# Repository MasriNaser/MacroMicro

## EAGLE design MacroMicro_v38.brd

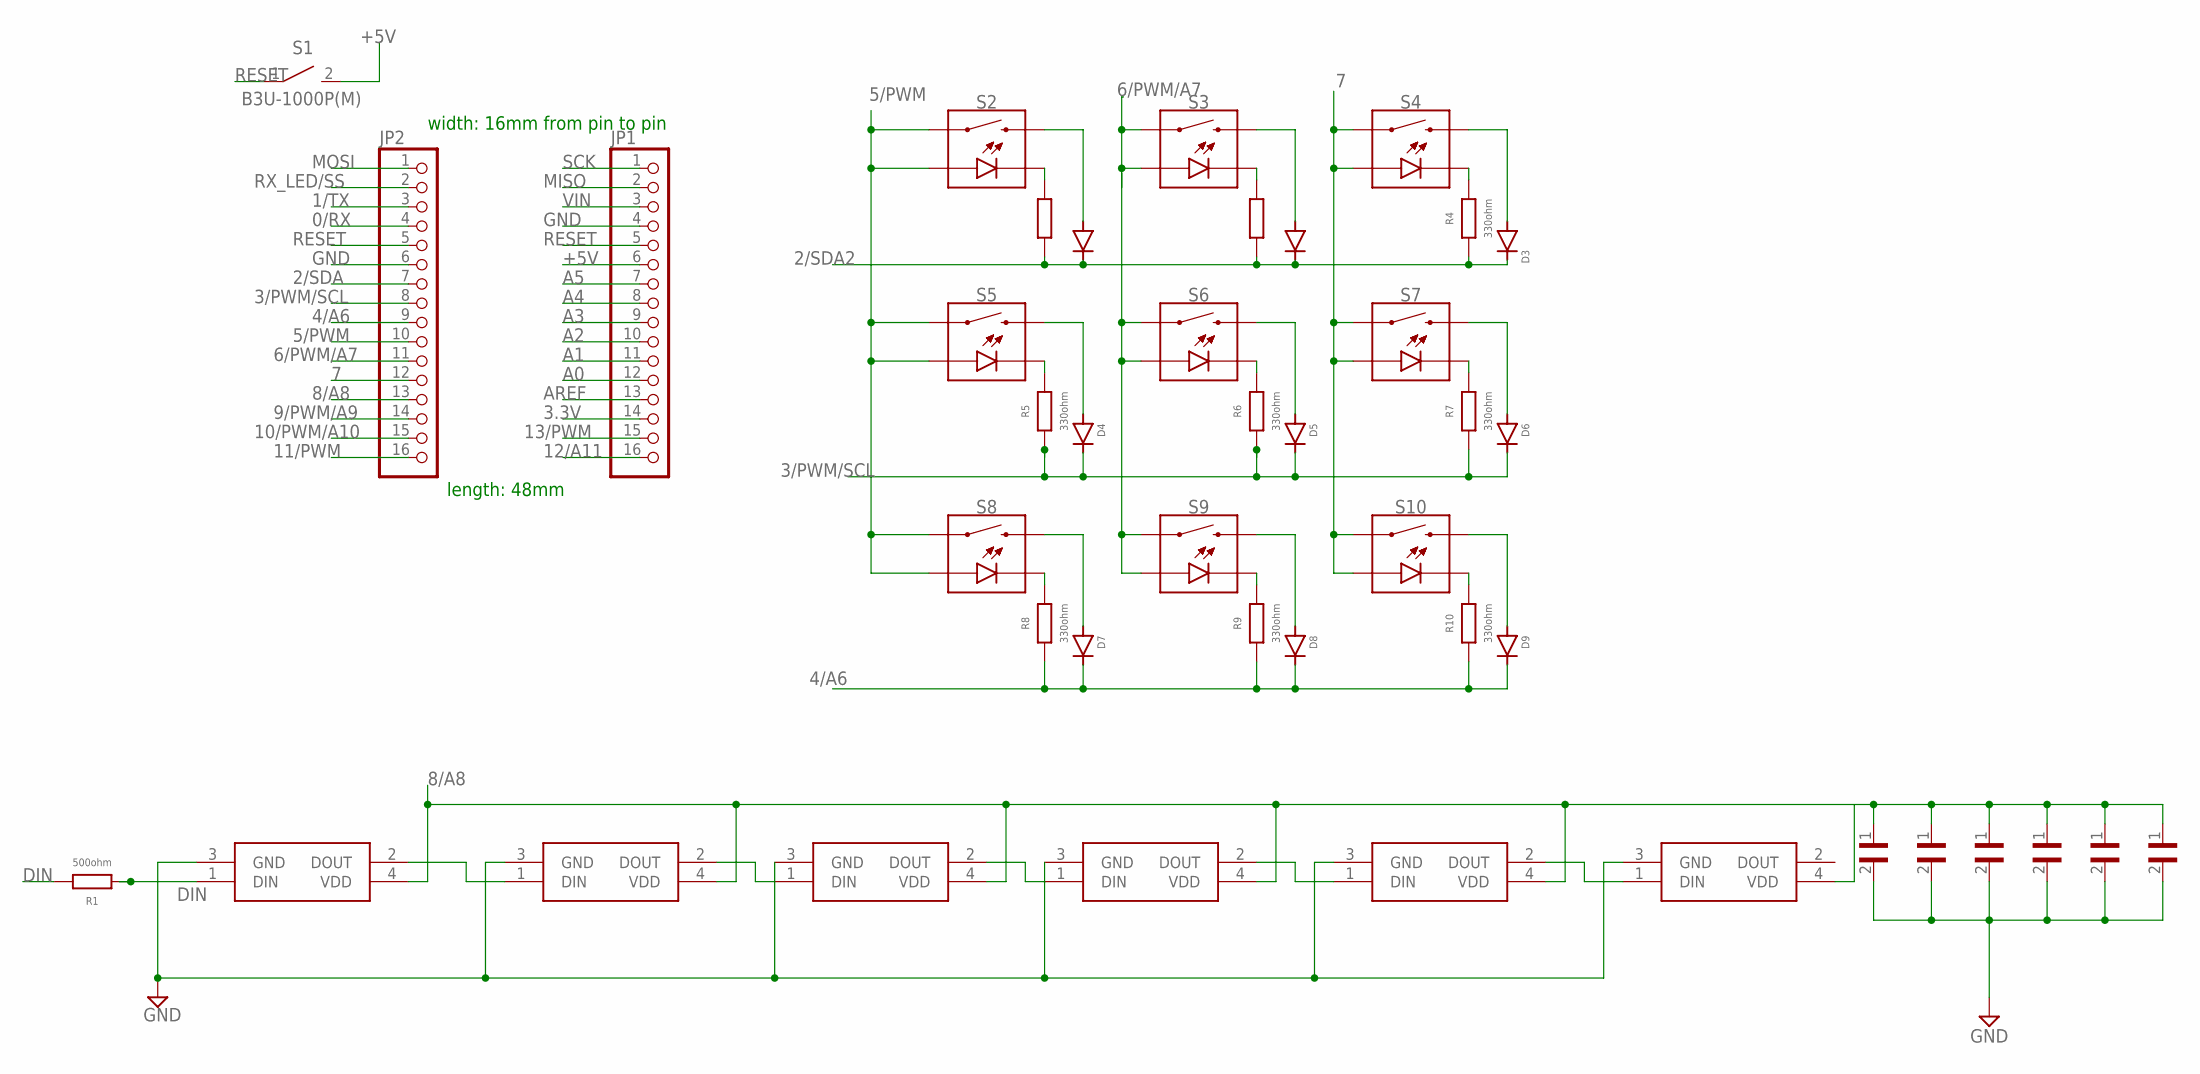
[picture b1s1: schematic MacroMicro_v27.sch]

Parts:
C1, C2, C3, C4, C5, C6: 0.1uf; CAPC1608X80N
D1, D2, D3, D4, D5, D6, D7, D8, D9: 1N4148WS; SOD-323
JP1, JP2: PINHD-1X16; 1X16
LED1, LED2, LED3, LED4, LED5, LED6: SK6812MINI-E; SK6812MINIE
R1: 500ohm; RESC3216X70
R2, R3, R4, R5, R6, R7, R8, R9, R10: 330ohm; RESC3216X70
S1: B3U-1000P(M)
S2, S3, S4, S5, S6, S7, S8, S9, S10: MOMENTARY-SWITCH-SPST-LED-PTH-CHERRY; CHERRY-MX-LED

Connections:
0/RX: JP2.4
1/TX: JP2.3
2/SDA: JP2.7
2/SDA2: D1.C, D2.C, D3.C, R2.1, R3.1, R4.1
3.3V: JP1.14
3/PWM/SCL: D4.C, D5.C, D6.C, JP2.8, R5.1, R6.1, R7.1
4/A6: D7.C, D8.C, D9.C, JP2.9, R8.1, R9.1, R10.1
5/PWM: JP2.10, S2.A, S2.S1 (1), S5.A, S5.S1 (1), S8.A, S8.S1 (1)
6/PWM/A7: JP2.11, S3.A, S3.S1 (1), S6.A, S6.S1 (1), S9.A, S9.S1 (1)
7: JP2.12, S4.A, S4.S1 (1), S7.A, S7.S1 (1), S10.A, S10.S1 (1)
8/A8: C1.1, C2.1, C3.1, C4.1, C5.1, C6.1, JP2.13, LED1.4 (VDD), LED2.4 (VDD), LED3.4 (VDD), LED4.4 (VDD), LED5.4 (VDD), LED6.4 (VDD)
9/PWM/A9: JP2.14
10/PWM/A10: JP2.15
11/PWM: JP2.16
12/A11: JP1.16
13/PWM: JP1.15
+5V: JP1.6, S1.2
A0: JP1.12
A1: JP1.11
A2: JP1.10
A3: JP1.9
A4: JP1.8
A5: JP1.7
AREF: JP1.13
DIN: LED1.1 (DIN), R1.1, R1.2
GND: C1.2, C2.2, C3.2, C4.2, C5.2, C6.2, JP1.4, JP2.6, LED1.3 (GND), LED2.3 (GND), LED3.3 (GND), LED4.3 (GND), LED5.3 (GND), LED6.3 (GND)
MISO: JP1.2
MOSI: JP2.1
unnamed: D1.A, S2.S2 (2)
unnamed: D2.A, S3.S2 (2)
unnamed: R3.2, S3.K (C)
unnamed: D3.A, S4.S2 (2)
unnamed: R4.2, S4.K (C)
unnamed: D4.A, S5.S2 (2)
unnamed: R5.2, S5.K (C)
unnamed: D5.A, S6.S2 (2)
unnamed: LED1.2 (DOUT), LED2.1 (DIN)
unnamed: R2.2, S2.K (C)
unnamed: R6.2, S6.K (C)
unnamed: LED2.2 (DOUT), LED3.1 (DIN)
unnamed: D6.A, S7.S2 (2)
unnamed: R7.2, S7.K (C)
unnamed: LED3.2 (DOUT), LED4.1 (DIN)
unnamed: D7.A, S8.S2 (2)
unnamed: R8.2, S8.K (C)
unnamed: D8.A, S9.S2 (2)
unnamed: R9.2, S9.K (C)
unnamed: D9.A, S10.S2 (2)
unnamed: R10.2, S10.K (C)
unnamed: LED4.2 (DOUT), LED5.1 (DIN)
unnamed: LED5.2 (DOUT), LED6.1 (DIN)
RESET: JP1.5, JP2.5, S1.1
RX_LED/SS: JP2.2
SCK: JP1.1
VIN: JP1.3

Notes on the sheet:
width: 16mm from pin to pin
length: 48mm

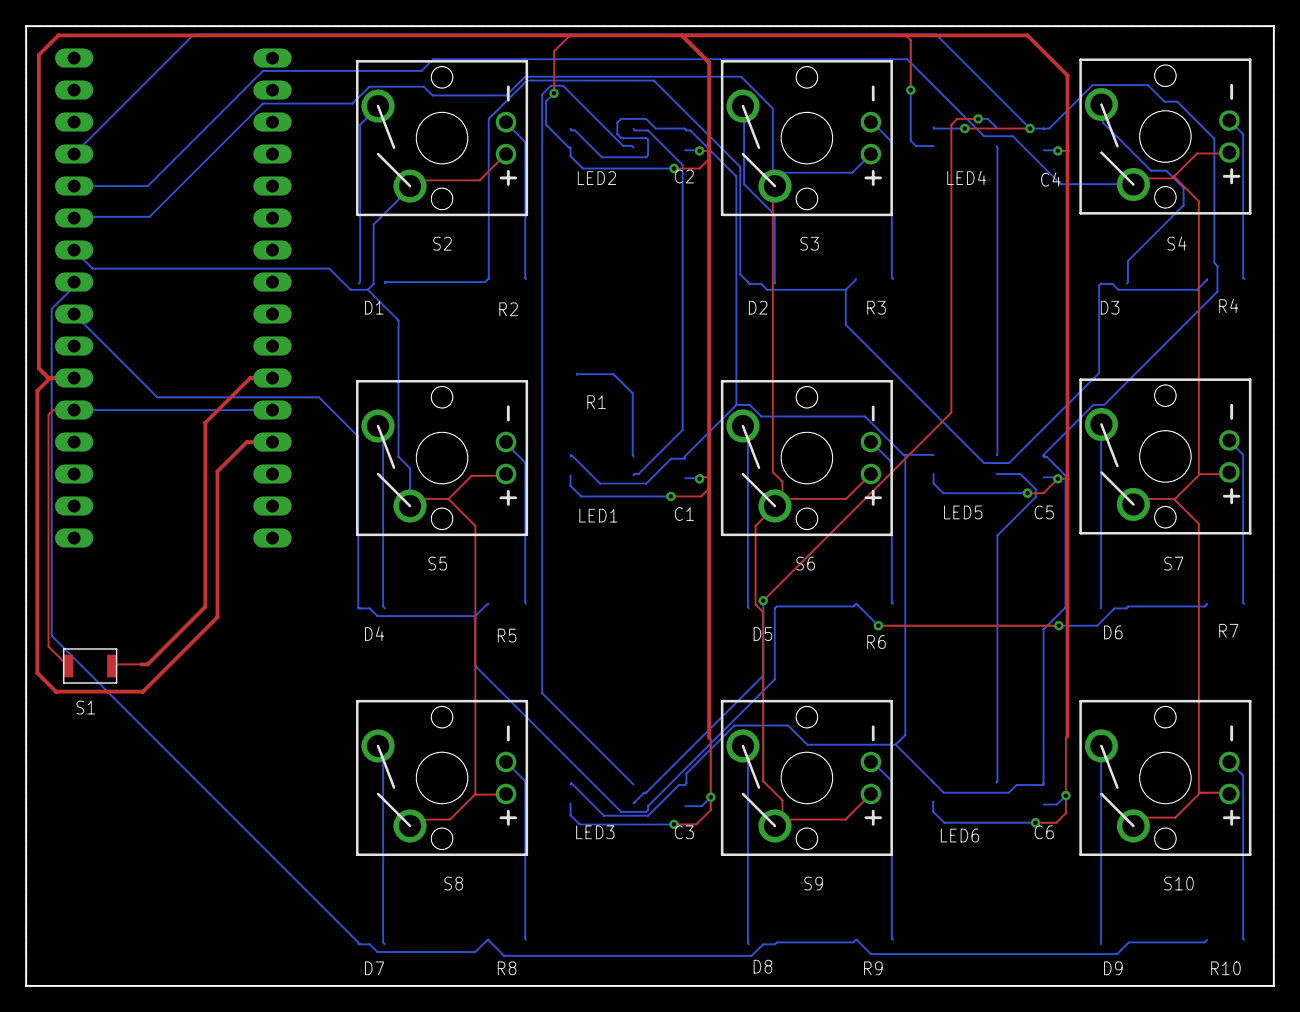
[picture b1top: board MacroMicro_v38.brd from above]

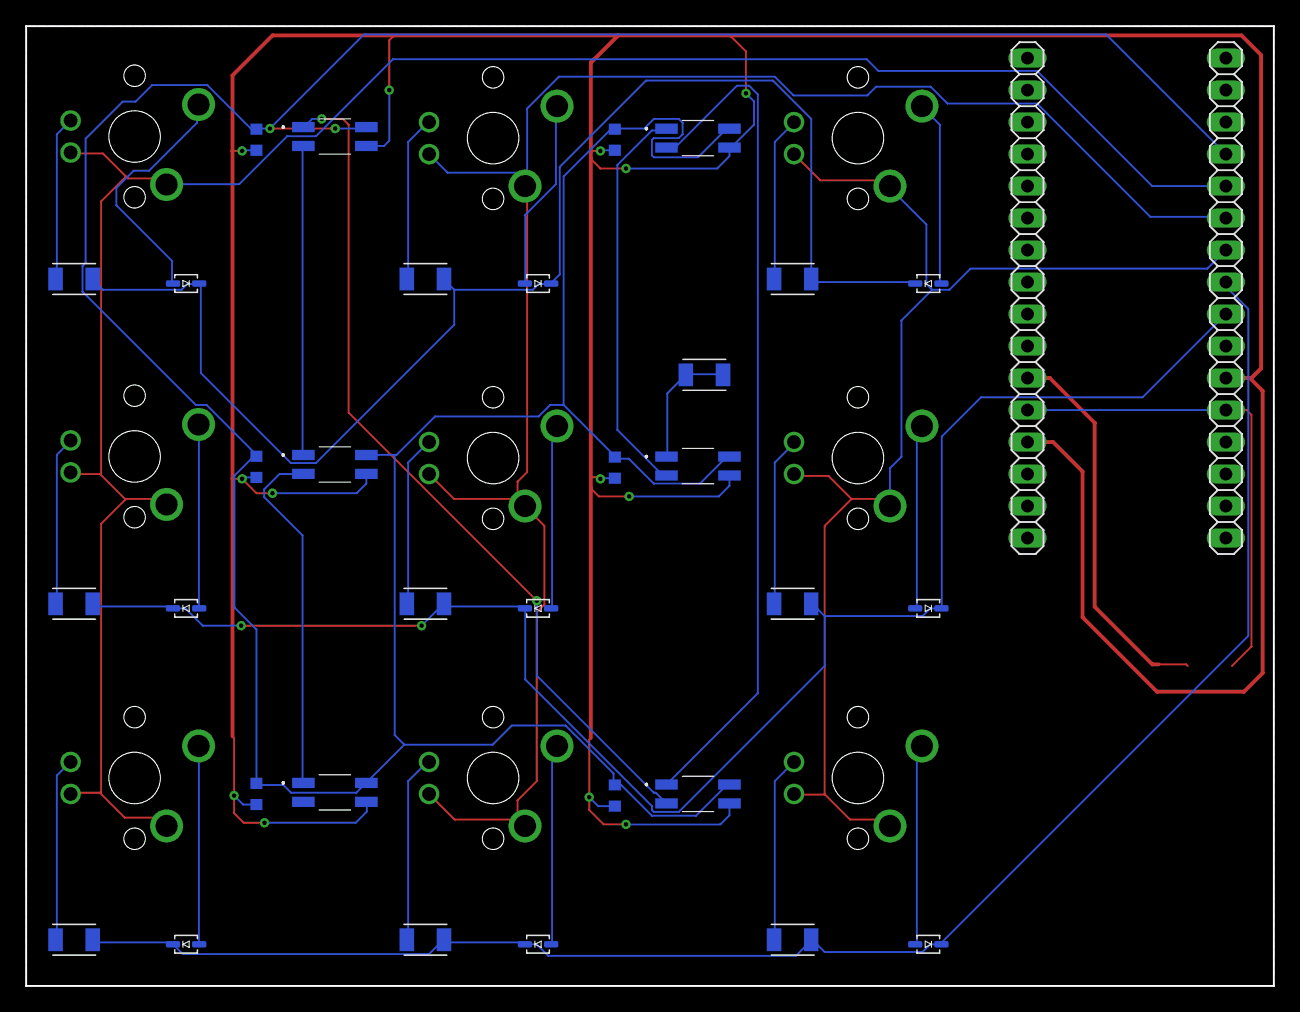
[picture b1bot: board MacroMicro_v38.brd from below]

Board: 2 copper layers, 99.1 x 76.2 mm, 43 parts (33 on the bottom side), 34 nets.

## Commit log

2021-04-02 arduino micro
2021-04-26 add gerber file

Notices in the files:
parts and their libraries:
SparkFun-Switches: Licensing: Creative Commons ShareAlike 4.0 International - https://creativecommons.org/licenses/by-sa/4.0
